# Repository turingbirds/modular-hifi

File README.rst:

Modular HiFi
============

A collection of Eurorack modules for home HiFi.

Typically, the PCB serves as a front panel while also carrying the circuit components on the back.

*Status: working prototypes. More documentation will follow!*

Modules
-------

Stereo mixer
~~~~~~~~~~~~

``stereo_3ch_mixer``

Three vertical slider potentiometers. Secondary (monitor) output. Quasi-differential inputs.

Phonograph preamplifier
~~~~~~~~~~~~~~~~~~~~~~~

``phono_preamp``

RIAA preamplifier and subsonic high-pass filter. 

Based on Rod Elliot <http://sound-au.com/> "Project 06" (RIAA pre-amp) and "Project 99" (subsonic filter)

Surround decoder
~~~~~~~~~~~~~~~~

``surround_decoder``

Stereo to 5.1 decoder. Separate volume controls for front, center, rear and subwoofer. Switchable subwoofer low-pass filter, adjustable between 50 and 500 Hz. Rear center channel "mix-in" control.

License
-------

`Open source hardware <https://www.oshwa.org/>`_ is hardware for which the design is made publicly available, so that anyone can study, modify, distribute, make, and sell the design or hardware based on that design, subject to the following license conditions.

Hardware licensed under the *CERN Open Hardware Licence Version 2 - Weakly Reciprocal,* a copy of which is included in this repository at `cern_ohl_w_v2.txt <https://github.com/turingbirds/modular-hifi/blob/master/cern_ohl_w_v2.txt>`_.

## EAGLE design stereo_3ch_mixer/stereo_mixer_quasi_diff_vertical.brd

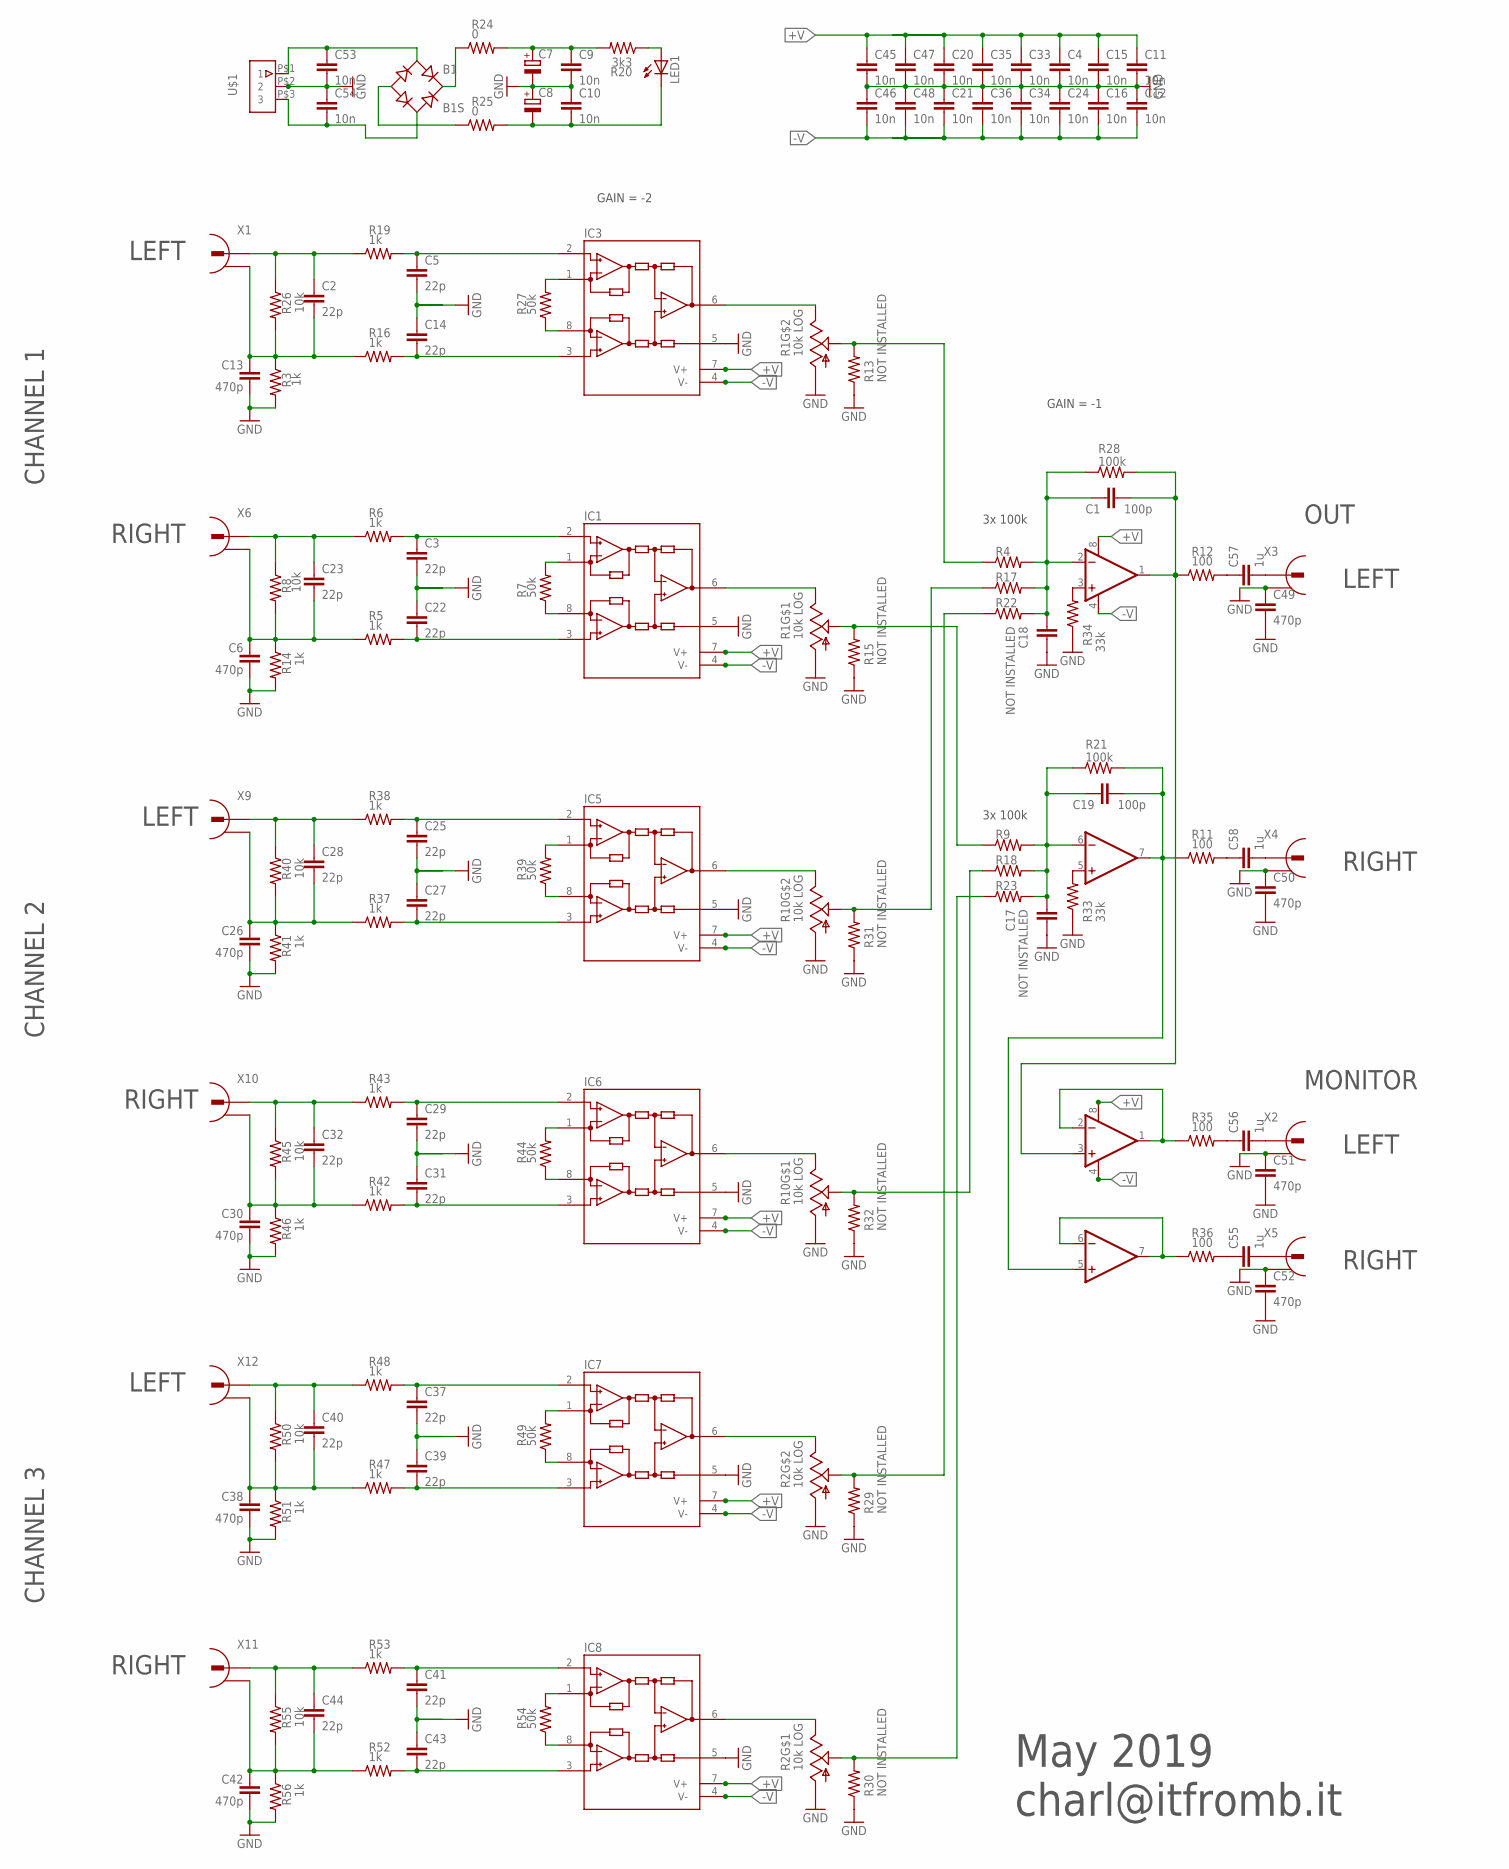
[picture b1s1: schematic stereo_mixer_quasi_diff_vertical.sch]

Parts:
B1: B1S; MBS
C1, C19: 100p; C1206
C2, C3, C5, C14, C22, C23, C25, C27, C28, C29, C31, C32, C37, C39, C40, C41, C43, C44: 22p; C1206
C4, C9, C10, C11, C12, C15, C16, C20, C21, C24, C33, C34, C35, C36, C45, C46, C47, C48, C53, C54: 10n; C1206
C6, C13, C26, C30, C38, C42, C49, C50, C51, C52: 470p; C1206
C7, C8: CPOL-EUSANYO_SMD_F12; SANYO-OSCON_SMD_F12
C17, C18: NOT INSTALLED; C1206
C55, C56, C57, C58: 1u; C1206
IC1, IC3, IC5, IC6, IC7, IC8: INA118U; SO08
IC2, IC4: OPAMP-DUALU; SO08
LED1: LEDCHIPLED_1206; CHIPLED_1206
R1, R2, R10: 10k LOG; SLIDE_POT_REAR_CONN
R3, R5, R6, R14, R16, R19, R37, R38, R41, R42, R43, R46, R47, R48, R51, R52, R53, R56: 1k; M1206
R4, R9, R17, R18, R21, R22, R23, R28: 100k; M1206
R7, R27, R39, R44, R49, R54: 50k; M1206
R8, R26, R40, R45, R50, R55: 10k; M1206
R11, R12, R35, R36: 100; M1206
R13, R15, R29, R30, R31, R32: NOT INSTALLED; M1206
R20: 3k3; M1206
R24, R25: 0; M1206
R33, R34: 33k; M1206
U$1: 3-PIN-JST-CONN-1.25MM-PITCH; S3B-PH-VERTICAL
X1, X6, X9, X10, X11, X12: 736880-49RCA-REAR-MOUNT; RCA-REAR-MOUNT
X2, X3, X4, X5: 736880-49; RCA-REAR-MOUNT-CENTER-ONLY

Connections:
+V: C4.1, C7.+, C9.1, C11.1, C15.1, C20.1, C33.1, C35.1, C45.1, C47.1, IC1.7 (V+), IC2.8 (V+), IC3.7 (V+), IC4.8 (V+), IC5.7 (V+), IC6.7 (V+), IC7.7 (V+), IC8.7 (V+), R20.2, R24.2
-V: C8.-, C10.2, C12.2, C16.2, C21.2, C24.2, C34.2, C36.2, C46.2, C48.2, IC1.4 (V-), IC2.4 (V-), IC3.4 (V-), IC4.4 (V-), IC5.4 (V-), IC6.4 (V-), IC7.4 (V-), IC8.4 (V-), LED1.C, R25.2
GND: C3.2, C4.2, C5.2, C6.2, C7.-, C8.+, C9.2, C10.1, C11.2, C12.1, C13.2, C14.1, C15.2, C16.1, C17.1, C18.1, C20.2, C21.1, C22.1, C24.1, C25.2, C26.2, C27.1, C29.2, C30.2, C31.1, C33.2, C34.1, C35.2, C36.1, C37.2, C38.2, C39.1, C41.2, C42.2, C43.1, C45.2, C46.1, C47.2, C48.1, C49.1, C49.2, C50.1, C50.2, C51.1, C51.2, C52.1, C52.2, C53.2, C54.1, IC1.5 (REF), IC3.5 (REF), IC5.5 (REF), IC6.5 (REF), IC7.5 (REF), IC8.5 (REF), R1.R1A (RA), R1.R2A (RA), R2.R1A (RA), R2.R2A (RA), R3.2, R10.R1A (RA), R10.R2A (RA), R13.1, R14.2, R15.1, R29.1, R30.1, R31.1, R32.1, R33.1, R34.1, R41.2, R46.2, R51.2, R56.2, U$1.P$2 (2), X2.SIGNAL (2), X3.SIGNAL (2), X4.SIGNAL (2), X5.SIGNAL (2)
unnamed: IC4.1 (OUT), IC4.2 (-IN), R35.1
unnamed: C2.1, R19.1, R26.1, X1.SIGNAL (1)
unnamed: C37.1, IC7.2 (-IN), R48.2
unnamed: IC3.6 (OUT), R1.R2B (RB)
unnamed: IC2.5 (+IN), R33.2
unnamed: R1.R2W (RW), R4.1, R13.2
unnamed: C38.1, C40.2, R47.1, R50.2, R51.1, X12.RING (2)
unnamed: R1.R1W (RW), R9.1, R15.2
unnamed: C19.2, IC2.7 (OUT), IC4.5 (+IN), R11.1, R21.2
unnamed: IC3.1 (RG), R27.2
unnamed: C3.1, IC1.2 (-IN), R6.2
unnamed: C25.1, IC5.2 (-IN), R38.2
unnamed: C6.1, C23.2, R5.1, R8.2, R14.1, X6.RING (2)
unnamed: C14.2, IC3.3 (+IN), R16.2
unnamed: C5.1, IC3.2 (-IN), R19.2
unnamed: C2.2, C13.1, R3.1, R16.1, R26.2, X1.RING (2)
unnamed: IC2.3 (+IN), R34.2
unnamed: C1.1, C18.2, IC2.2 (-IN), R4.2, R17.2, R22.2, R28.1
unnamed: C17.2, C19.1, IC2.6 (-IN), R9.2, R18.2, R21.1, R23.2
unnamed: C23.1, R6.1, R8.1, X6.SIGNAL (1)
unnamed: IC1.8 (RG), R7.1
unnamed: IC3.8 (RG), R27.1
unnamed: C22.2, IC1.3 (+IN), R5.2
unnamed: IC1.6 (OUT), R1.R1B (RB)
unnamed: R2.R2W (RW), R22.1, R29.2
unnamed: R2.R1W (RW), R23.1, R30.2
unnamed: IC1.1 (RG), R7.2
unnamed: B1.AC1, C53.1, U$1.P$1 (1)
unnamed: B1.+, R24.1
unnamed: B1.AC2, C54.2, U$1.P$3 (3)
unnamed: B1.-, R25.1
unnamed: IC4.6 (-IN), IC4.7 (OUT), R36.1
unnamed: LED1.A, R20.1
unnamed: C40.1, R48.1, R50.1, X12.SIGNAL (1)
unnamed: C1.2, IC2.1 (OUT), IC4.3 (+IN), R12.1, R28.2
unnamed: C26.1, C28.2, R37.1, R40.2, R41.1, X9.RING (2)
unnamed: C28.1, R38.1, R40.1, X9.SIGNAL (1)
unnamed: IC5.8 (RG), R39.1
unnamed: C27.2, IC5.3 (+IN), R37.2
unnamed: IC6.6 (OUT), R10.R1B (RB)
unnamed: IC5.1 (RG), R39.2
unnamed: C29.1, IC6.2 (-IN), R43.2
unnamed: C30.1, C32.2, R42.1, R45.2, R46.1, X10.RING (2)
unnamed: C32.1, R43.1, R45.1, X10.SIGNAL (1)
unnamed: IC6.8 (RG), R44.1
unnamed: C31.2, IC6.3 (+IN), R42.2
unnamed: IC5.6 (OUT), R10.R2B (RB)
unnamed: IC6.1 (RG), R44.2
unnamed: R10.R2W (RW), R17.1, R31.2
unnamed: R10.R1W (RW), R18.1, R32.2
unnamed: IC7.8 (RG), R49.1
unnamed: C39.2, IC7.3 (+IN), R47.2
unnamed: IC7.1 (RG), R49.2
unnamed: C41.1, IC8.2 (-IN), R53.2
unnamed: C42.1, C44.2, R52.1, R55.2, R56.1, X11.RING (2)
unnamed: C44.1, R53.1, R55.1, X11.SIGNAL (1)
unnamed: IC8.8 (RG), R54.1
unnamed: C43.2, IC8.3 (+IN), R52.2
unnamed: IC8.1 (RG), R54.2
unnamed: IC8.6 (OUT), R2.R1B (RB)
unnamed: IC7.6 (OUT), R2.R2B (RB)
unnamed: C55.1, R36.2
unnamed: C56.1, R35.2
unnamed: C57.1, R12.2
unnamed: C58.1, R11.2
unnamed: C57.2, X3.RING (1)
unnamed: C58.2, X4.RING (1)
unnamed: C56.2, X2.RING (1)
unnamed: C55.2, X5.RING (1)

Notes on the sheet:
CHANNEL 1
LEFT
RIGHT
OUT
CHANNEL 2
CHANNEL 3
MONITOR
GAIN = -2
GAIN = -1
3x 100k
May 2019 charl@itfromb.it

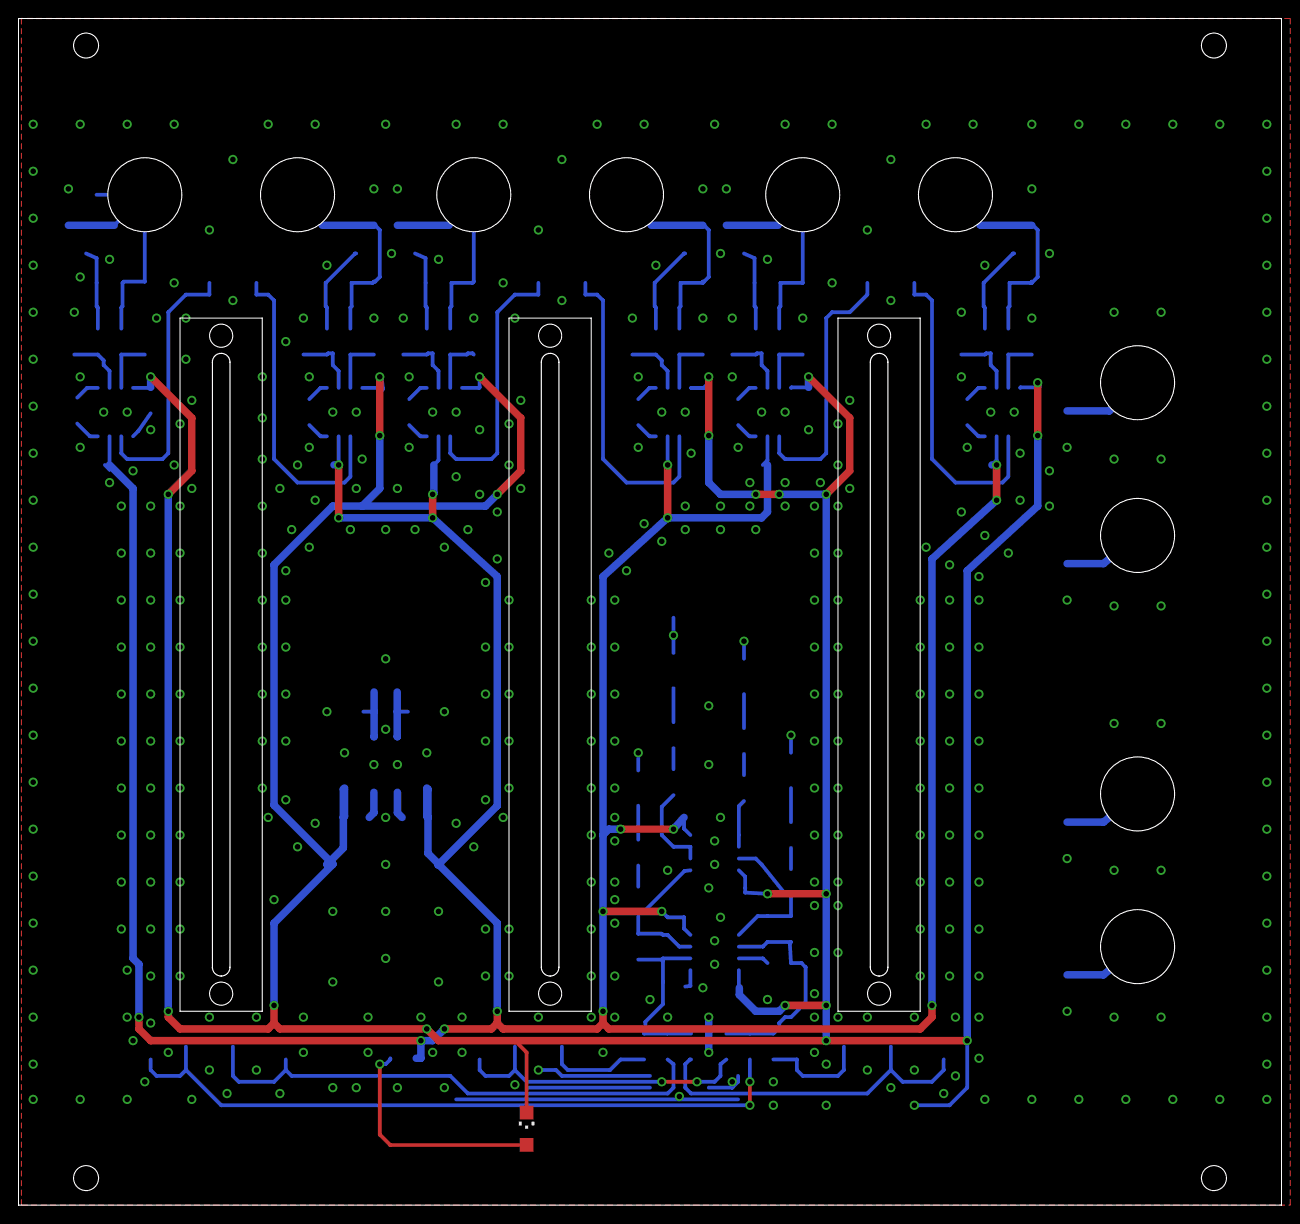
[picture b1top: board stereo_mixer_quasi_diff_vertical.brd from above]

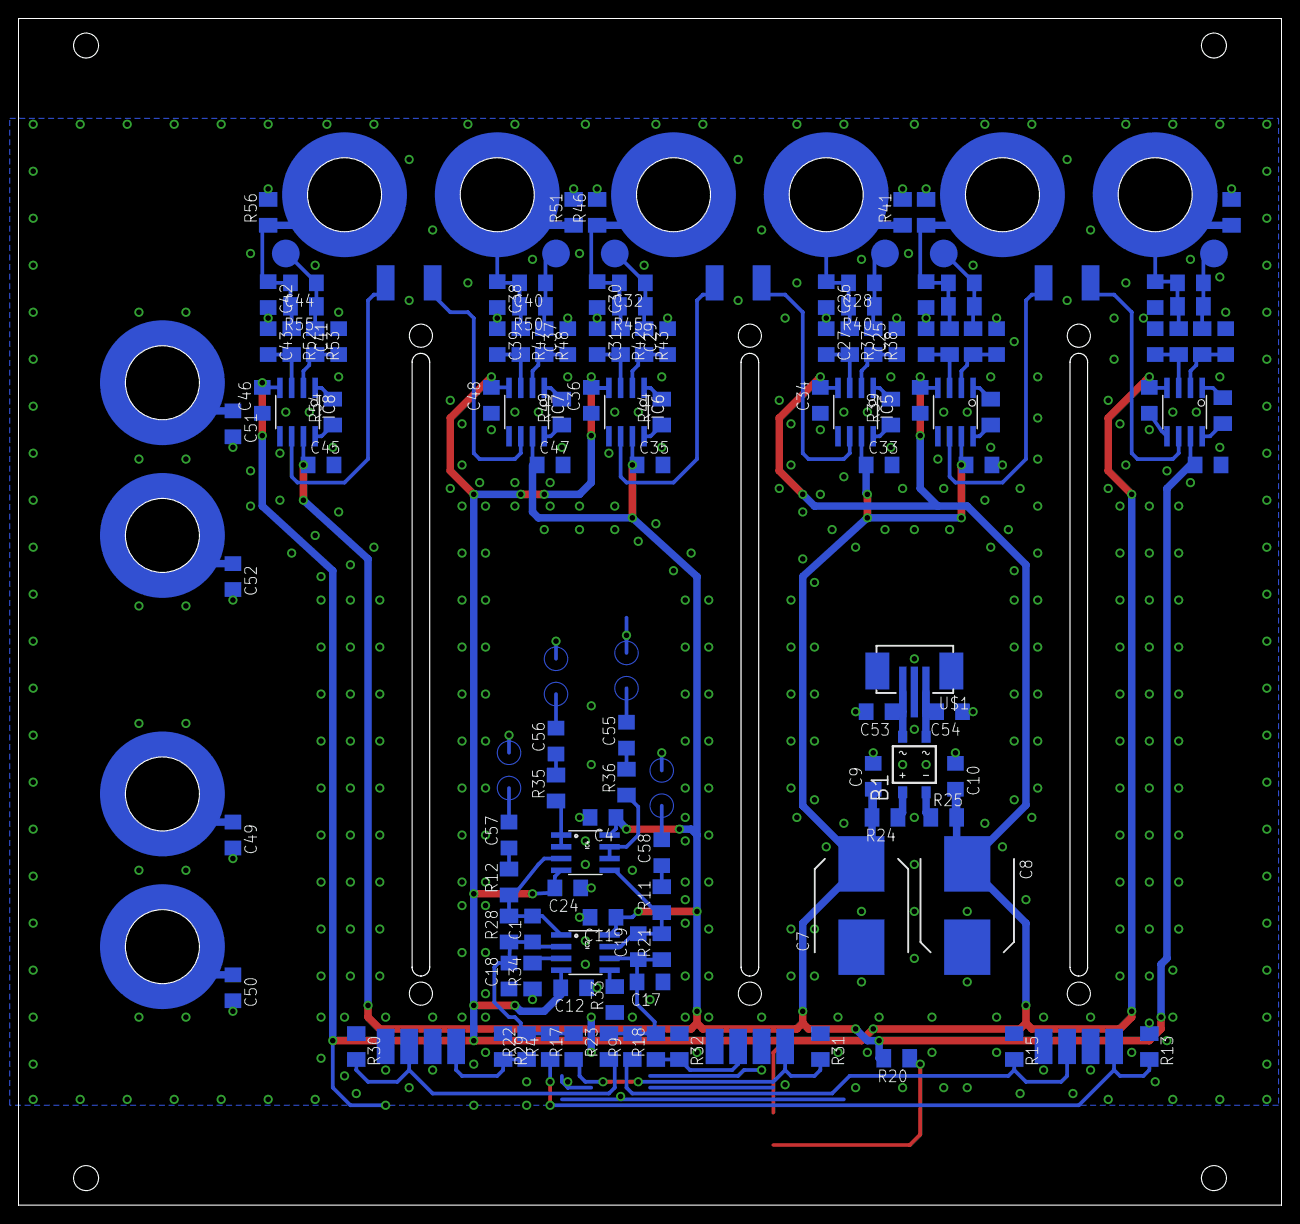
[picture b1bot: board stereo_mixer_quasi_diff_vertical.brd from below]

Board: 2 copper layers, 136.5 x 128.3 mm, 135 parts (121 on the bottom side), 72 nets.

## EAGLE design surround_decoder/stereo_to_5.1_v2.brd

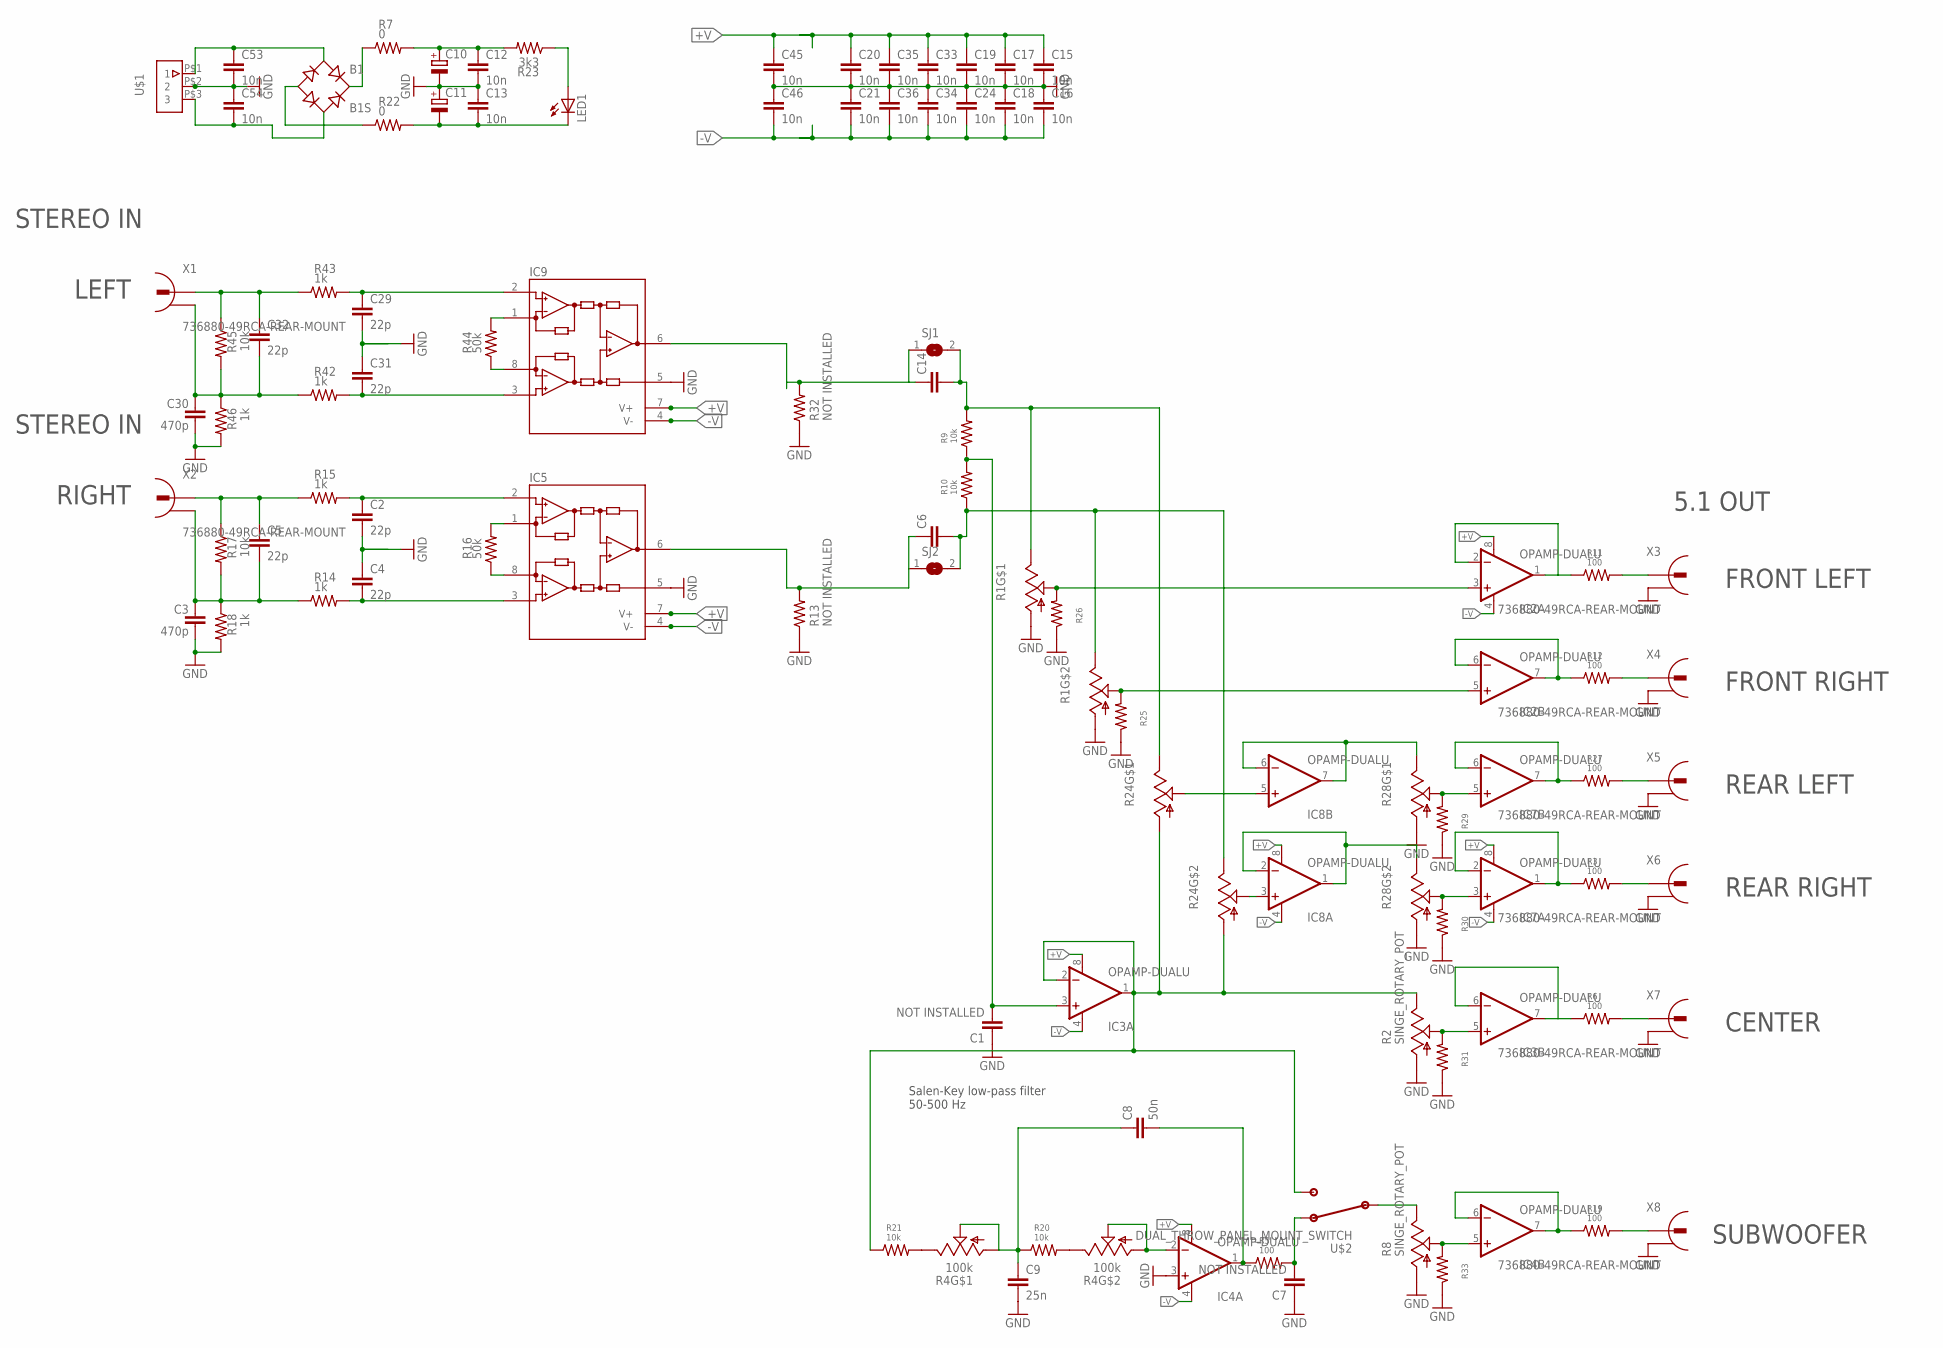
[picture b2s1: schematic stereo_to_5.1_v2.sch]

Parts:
B1: B1S; MBS
C1, C7: NOT INSTALLED; C1206
C2, C4, C5, C29, C31, C32: 22p; C1206
C3, C30: 470p; C1206
C6, C14: C-EUC4532; C4532
C8: 50n; C1206
C9: 25n; C1206
C10, C11: CPOL-EUSANYO_SMD_F12; SANYO-OSCON_SMD_F12
C12, C13, C15, C16, C17, C18, C19, C20, C21, C24, C33, C34, C35, C36, C45, C46, C53, C54: 10n; C1206
IC2, IC3, IC4, IC7, IC8: OPAMP-DUALU; SO08
IC5, IC9: ad620; SO08
LED1: LEDCHIPLED_1206; CHIPLED_1206
R1, R24, R28: TRIM_US-ROTARY; DUAL_GANGED_ROTARY_POT
R2, R8: SINGE_ROTARY_POT; SINGLE_ROTARY_POT
R3, R5, R6, R11, R12, R19, R27: 100; M1206
R4: 100k; DUAL_GANGED_ROTARY_POT
R7, R22: 0; M1206
R9, R10, R17, R20, R21, R45: 10k; M1206
R13, R32: NOT INSTALLED; M1206
R14, R15, R18, R42, R43, R46: 1k; M1206
R16, R44: 50k; M1206
R23: 3k3; M1206
R25, R26, R29, R30, R31, R33: R-US_M1206; M1206
SJ1, SJ2: SJ
U$1: 3-PIN-JST-CONN-1.25MM-PITCH; S3B-PH-VERTICAL
U$2: DUAL_THROW_PANEL_MOUNT_SWITCH; PANEL_MOUNT_DUAL_THROW_SWITCH
X1, X2, X3, X4, X5, X6, X7, X8: 736880-49RCA-REAR-MOUNT; RCA-REAR-MOUNT

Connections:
+V: C10.+, C12.1, C15.1, C17.1, C19.1, C20.1, C33.1, C35.1, C45.1, IC2.8 (V+), IC3.8 (V+), IC4.8 (V+), IC5.7 (V+), IC7.8 (V+), IC8.8 (V+), IC9.7 (V+), R7.2, R23.2
-V: C11.-, C13.2, C16.2, C18.2, C21.2, C24.2, C34.2, C36.2, C46.2, IC2.4 (V-), IC3.4 (V-), IC4.4 (V-), IC5.4 (V-), IC7.4 (V-), IC8.4 (V-), IC9.4 (V-), LED1.C, R22.2
GND: C1.1, C2.2, C3.2, C4.1, C7.1, C9.2, C10.-, C11.+, C12.2, C13.1, C15.2, C16.1, C17.2, C18.1, C19.2, C20.2, C21.1, C24.1, C29.2, C30.2, C31.1, C33.2, C34.1, C35.2, C36.1, C45.2, C46.1, C53.2, C54.1, IC4.3 (+IN), IC5.5 (REF), IC9.5 (REF), R1.P$2 (RA), R1.P$5 (RA), R2.P$2 (RA), R8.P$2 (RA), R13.1, R18.2, R25.1, R26.1, R28.P$2 (RA), R28.P$5 (RA), R29.1, R30.1, R31.1, R32.1, R33.1, R46.2, U$1.P$2 (2), X3.RING (2), X4.RING (2), X5.RING (2), X6.RING (2), X7.RING (2), X8.RING (2)
unnamed: C14.2, R1.P$3 (RB), R9.2, R24.P$3 (RB), SJ1.2
unnamed: C7.2, R5.2, U$2.LEFT (NC)
unnamed: R8.P$3 (RB), U$2.MIDDLE (COMMON)
unnamed: IC4.5 (+IN), R8.P$1 (RW), R33.2
unnamed: IC4.6 (-IN), IC4.7 (OUT), R19.1
unnamed: C6.2, R1.P$6 (RB), R10.1, R24.P$6 (RB), SJ2.2
unnamed: IC7.5 (+IN), R28.P$1 (RW), R29.2
unnamed: IC2.1 (OUT), IC2.2 (-IN), R11.1
unnamed: IC2.3 (+IN), R1.P$1 (RW), R26.2
unnamed: IC2.5 (+IN), R1.P$4 (RW), R25.2
unnamed: IC2.6 (-IN), IC2.7 (OUT), R12.1
unnamed: IC3.5 (+IN), R2.P$1 (RW), R31.2
unnamed: R11.2, X3.SIGNAL (1)
unnamed: R12.2, X4.SIGNAL (1)
unnamed: C8.2, IC4.1 (OUT), R5.1
unnamed: IC7.3 (+IN), R28.P$4 (RW), R30.2
unnamed: C2.1, IC5.2 (-IN), R15.2
unnamed: C3.1, C5.2, R14.1, R17.2, R18.1, X2.RING (2)
unnamed: C5.1, R15.1, R17.1, X2.SIGNAL (1)
unnamed: IC5.8 (RG), R16.1
unnamed: C4.2, IC5.3 (+IN), R14.2
unnamed: IC5.1 (RG), R16.2
unnamed: C6.1, IC5.6 (OUT), R13.2, SJ2.1
unnamed: IC7.1 (OUT), IC7.2 (-IN), R3.1
unnamed: R3.2, X6.SIGNAL (1)
unnamed: R4.P$6 (RB), R20.2
unnamed: R4.P$3 (RB), R21.2
unnamed: C1.2, IC3.3 (+IN), R9.1, R10.2
unnamed: IC3.1 (OUT), IC3.2 (-IN), R2.P$3 (RB), R21.1, R24.P$2 (RA), R24.P$5 (RA), U$2.RIGHT (NO)
unnamed: IC7.6 (-IN), IC7.7 (OUT), R27.1
unnamed: IC3.6 (-IN), IC3.7 (OUT), R6.1
unnamed: R27.2, X5.SIGNAL (1)
unnamed: R6.2, X7.SIGNAL (1)
unnamed: IC8.5 (+IN), R24.P$1 (RW)
unnamed: IC8.3 (+IN), R24.P$4 (RW)
unnamed: IC8.1 (OUT), IC8.2 (-IN), R28.P$6 (RB)
unnamed: IC8.6 (-IN), IC8.7 (OUT), R28.P$3 (RB)
unnamed: R19.2, X8.SIGNAL (1)
unnamed: IC4.2 (-IN), R4.P$4 (RW), R4.P$5 (RA)
unnamed: C8.1, C9.1, R4.P$1 (RW), R4.P$2 (RA), R20.1
unnamed: B1.AC1, C53.1, U$1.P$1 (1)
unnamed: B1.+, R7.1
unnamed: C14.1, IC9.6 (OUT), R32.2, SJ1.1
unnamed: B1.AC2, C54.2, U$1.P$3 (3)
unnamed: C29.1, IC9.2 (-IN), R43.2
unnamed: C30.1, C32.2, R42.1, R45.2, R46.1, X1.RING (2)
unnamed: C32.1, R43.1, R45.1, X1.SIGNAL (1)
unnamed: IC9.8 (RG), R44.1
unnamed: C31.2, IC9.3 (+IN), R42.2
unnamed: B1.-, R22.1
unnamed: IC9.1 (RG), R44.2
unnamed: LED1.A, R23.1

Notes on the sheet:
STEREO IN
FRONT LEFT
FRONT RIGHT
REAR LEFT
REAR RIGHT
CENTER
SUBWOOFER
LEFT
RIGHT
5.1 OUT
Salen-Key low-pass filter 50-500 Hz

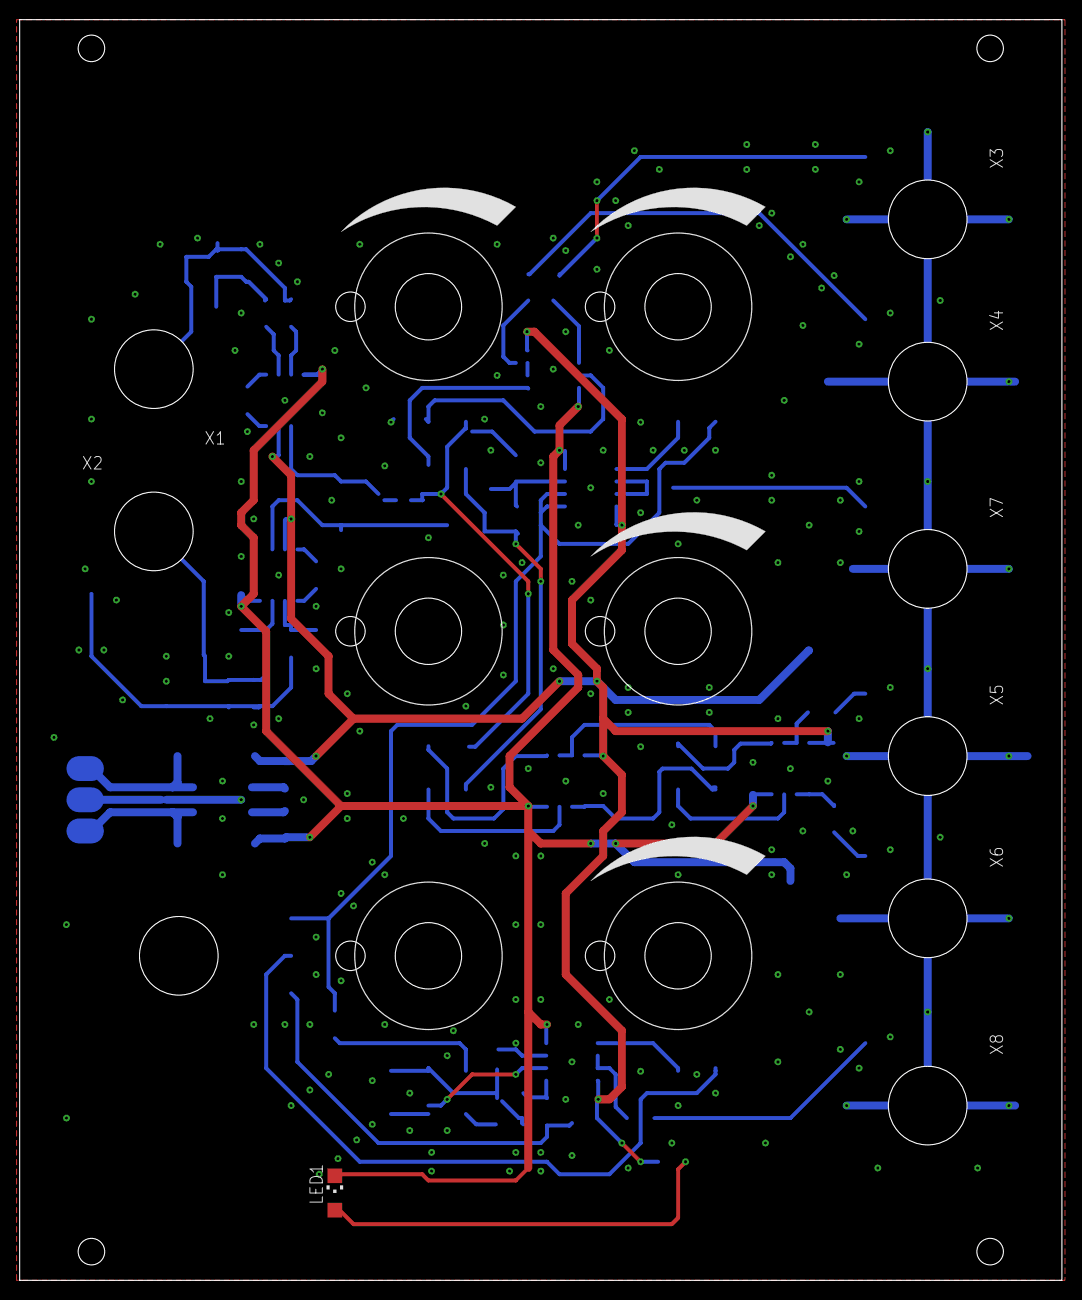
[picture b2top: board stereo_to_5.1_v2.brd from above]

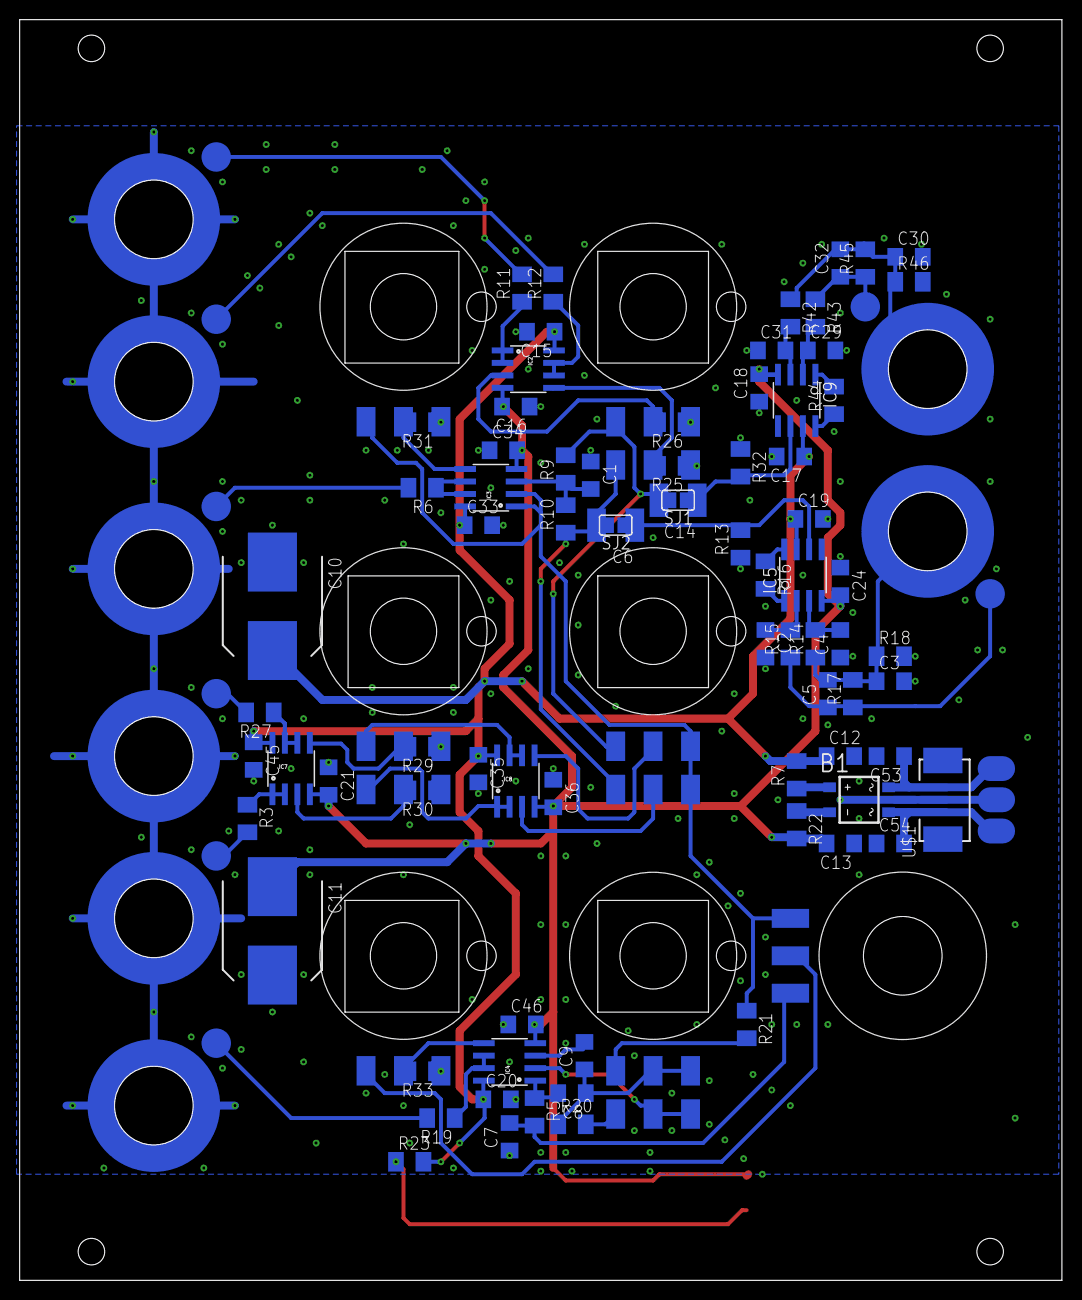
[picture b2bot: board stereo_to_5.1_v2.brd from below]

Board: 2 copper layers, 106.0 x 128.3 mm, 93 parts (77 on the bottom side), 55 nets.

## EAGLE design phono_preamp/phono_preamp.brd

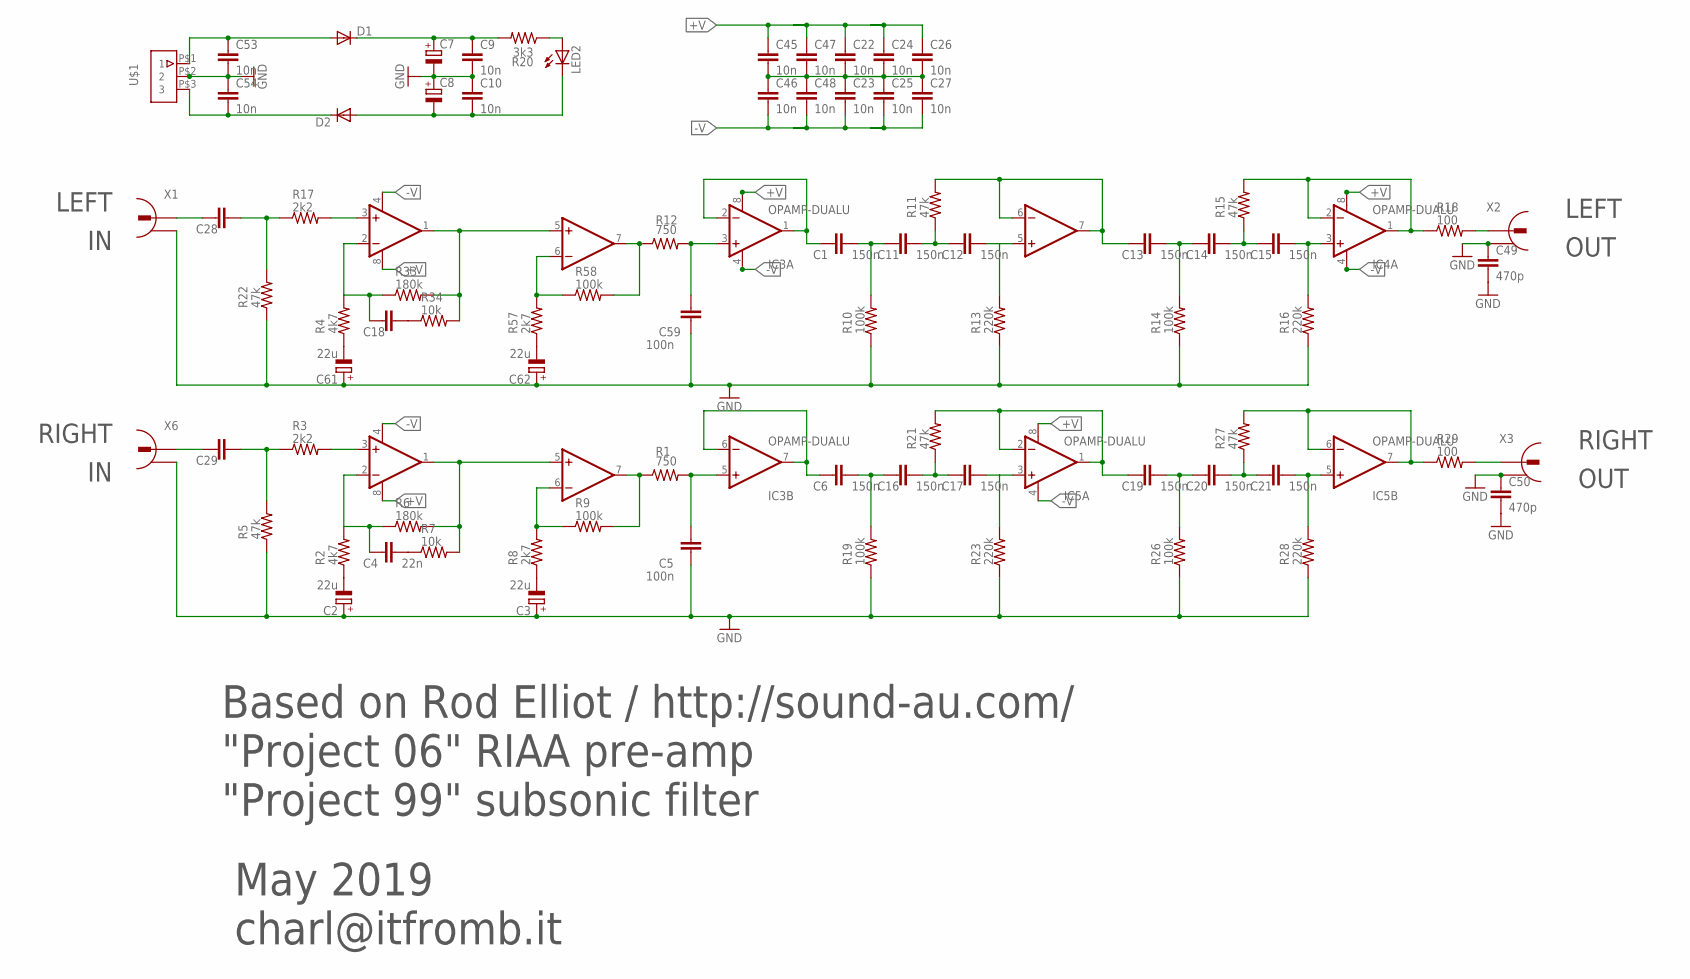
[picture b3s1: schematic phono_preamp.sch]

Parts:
C1, C6, C11, C12, C13, C14, C15, C16, C17, C19, C20, C21: 150n; C1206
C2, C3, C61, C62: 22u; PANASONIC_C
C4, C18: 22n; C1206
C5, C59: 100n; C1206
C7, C8: CPOL-EUSANYO_SMD_F12; SANYO-OSCON_SMD_F12
C9, C10, C22, C23, C24, C25, C26, C27, C45, C46, C47, C48, C53, C54: 10n; C1206
C28, C29: C-EUC1206; C1206
C49, C50: 470p; C1206
D1, D2: DIODE-DO214AA; DO214AA
IC1, IC2, IC3, IC4, IC5: OPAMP-DUALU; SO08
LED2: LEDCHIPLED_1206; CHIPLED_1206
R1, R12: 750; M1206
R2, R4: 4k7; M1206
R3, R17: 2k2; M1206
R5, R11, R15, R21, R22, R27: 47k; M1206
R6, R33: 180k; M1206
R7, R34: 10k; M1206
R8, R57: 2k7; M1206
R9, R10, R14, R19, R26, R58: 100k; M1206
R13, R16, R23, R28: 220k; M1206
R18, R29: 100; M1206
R20: 3k3; M1206
U$1: 3-PIN-JST-CONN-1.25MM-PITCH; S3B-PH-VERTICAL
X1, X2, X3, X6: 736880-49RCA-REAR-MOUNT; RCA-REAR-MOUNT

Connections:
+V: C7.+, C9.1, C22.1, C24.1, C26.1, C45.1, C47.1, D1.C, IC1.8 (V+), IC2.8 (V+), IC3.8 (V+), IC4.8 (V+), IC5.8 (V+), R20.2
-V: C8.-, C10.2, C23.2, C25.2, C27.2, C46.2, C48.2, D2.A, IC1.4 (V-), IC2.4 (V-), IC3.4 (V-), IC4.4 (V-), IC5.4 (V-), LED2.C
GND: C2.+, C3.+, C5.1, C7.-, C8.+, C9.2, C10.1, C22.2, C23.1, C24.2, C25.1, C26.2, C27.1, C45.2, C46.1, C47.2, C48.1, C49.1, C49.2, C50.1, C50.2, C53.2, C54.1, C59.1, C61.+, C62.+, R5.1, R10.1, R13.1, R14.1, R16.1, R19.1, R22.1, R23.1, R26.1, R28.1, U$1.P$2 (2), X1.RING (2), X2.RING (2), X3.RING (2), X6.RING (2)
unnamed: C1.1, IC3.1 (OUT), IC3.2 (-IN)
unnamed: C5.2, IC3.5 (+IN), R1.2
unnamed: C13.1, IC4.6 (-IN), IC4.7 (OUT), R11.2
unnamed: C2.-, R2.1
unnamed: C4.1, IC1.2 (-IN), R2.2, R6.1
unnamed: C61.-, R4.1
unnamed: C29.2, R3.1, R5.2
unnamed: IC1.3 (+IN), R3.2
unnamed: C4.2, R7.1
unnamed: IC1.1 (OUT), IC1.5 (+IN), R6.2, R7.2
unnamed: C3.-, R8.1
unnamed: IC1.6 (-IN), R8.2, R9.1
unnamed: IC1.7 (OUT), R1.1, R9.2
unnamed: C12.2, IC4.5 (+IN), R13.2
unnamed: C11.2, C12.1, R11.1
unnamed: C1.2, C11.1, R10.2
unnamed: R18.2, X2.SIGNAL (1)
unnamed: IC4.1 (OUT), IC4.2 (-IN), R15.2, R18.1
unnamed: C15.2, IC4.3 (+IN), R16.2
unnamed: C18.1, IC2.2 (-IN), R4.2, R33.1
unnamed: C14.2, C15.1, R15.1
unnamed: C28.2, R17.1, R22.2
unnamed: C13.2, C14.1, R14.2
unnamed: C6.1, IC3.6 (-IN), IC3.7 (OUT)
unnamed: C19.1, IC5.1 (OUT), IC5.2 (-IN), R21.2
unnamed: C17.2, IC5.3 (+IN), R23.2
unnamed: C16.2, C17.1, R21.1
unnamed: C6.2, C16.1, R19.2
unnamed: IC5.6 (-IN), IC5.7 (OUT), R27.2, R29.1
unnamed: C21.2, IC5.5 (+IN), R28.2
unnamed: C20.2, C21.1, R27.1
unnamed: C53.1, D1.A, U$1.P$1 (1)
unnamed: C54.2, D2.C, U$1.P$3 (3)
unnamed: C19.2, C20.1, R26.2
unnamed: LED2.A, R20.1
unnamed: R29.2, X3.SIGNAL (1)
unnamed: IC2.3 (+IN), R17.2
unnamed: C28.1, X1.SIGNAL (1)
unnamed: C29.1, X6.SIGNAL (1)
unnamed: IC2.7 (OUT), R12.1, R58.2
unnamed: C18.2, R34.1
unnamed: C59.2, IC3.3 (+IN), R12.2
unnamed: IC2.1 (OUT), IC2.5 (+IN), R33.2, R34.2
unnamed: C62.-, R57.1
unnamed: IC2.6 (-IN), R57.2, R58.1

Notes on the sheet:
LEFT
RIGHT
OUT
May 2019 charl@itfromb.it
Based on Rod Elliot / http://sound-au.com/ "Project 06" RIAA pre-amp "Project 99" subsonic filter

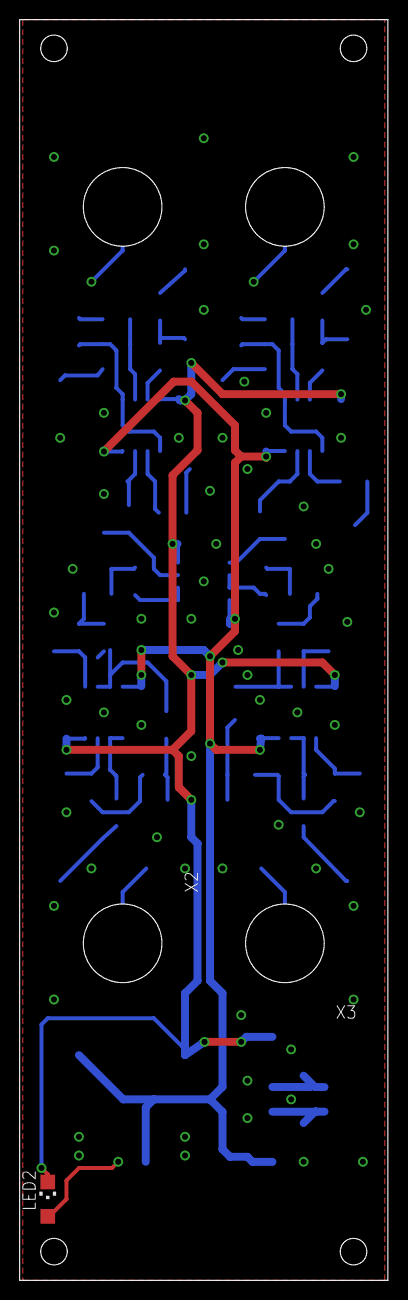
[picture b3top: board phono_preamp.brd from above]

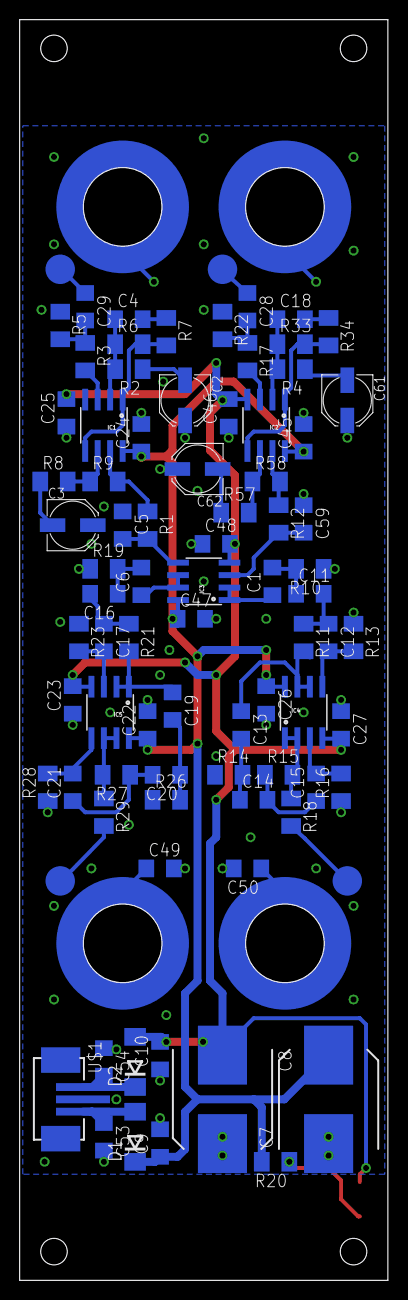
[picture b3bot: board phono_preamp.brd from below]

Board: 2 copper layers, 37.5 x 128.3 mm, 84 parts (79 on the bottom side), 48 nets.

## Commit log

2021-03-08 add PDF export of the schematic
2022-02-06 add license information
2022-02-10 remove software part of license; hardware-only project
